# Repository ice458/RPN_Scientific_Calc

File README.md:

# RPN Scientific Calculator
RPN Scientific Calculator with PIC32CM2532LE00048.  
Reverse Polish notation with 4-element stack.  
This calculator uses a proprietary decimal floating point library to perform calculations.  
This project was created using MPLAB X IDE v6.20, XC32 v4.35, and MCC v5.50.  
For more information, please visit [this site.](https://ice458.github.io/project-18775/)

## Demo

## License

This project is licensed under the MIT License. See the [LICENSE](LICENSE) file for details.

## Notice Regarding Third-Party Code

Please note that the copyright of the files contained in the directories [src/packs](src/packs) and [src/config](src/config) does not belong to ice458. These files include code that is subject to third-party licenses. Please refer to the comments at the top of these files for specific licensing information.

The directories [src/packs](src/packs) and [src/config](src/config) may contain files licensed under the Apache License 2.0 and Microchip's proprietary license. You must comply with these licenses when using or distributing these files.

### Apache License 2.0

Portions of this project are licensed under the Apache License 2.0. You may obtain a copy of the License at http://www.apache.org/licenses/LICENSE-2.0.

### Microchip Proprietary License

Certain files are subject to Microchip's proprietary license. These files are provided by Microchip "as is" without any warranties, and you may use Microchip software and any derivatives exclusively with Microchip products. Refer to the comments within the files for more details on the terms and conditions.

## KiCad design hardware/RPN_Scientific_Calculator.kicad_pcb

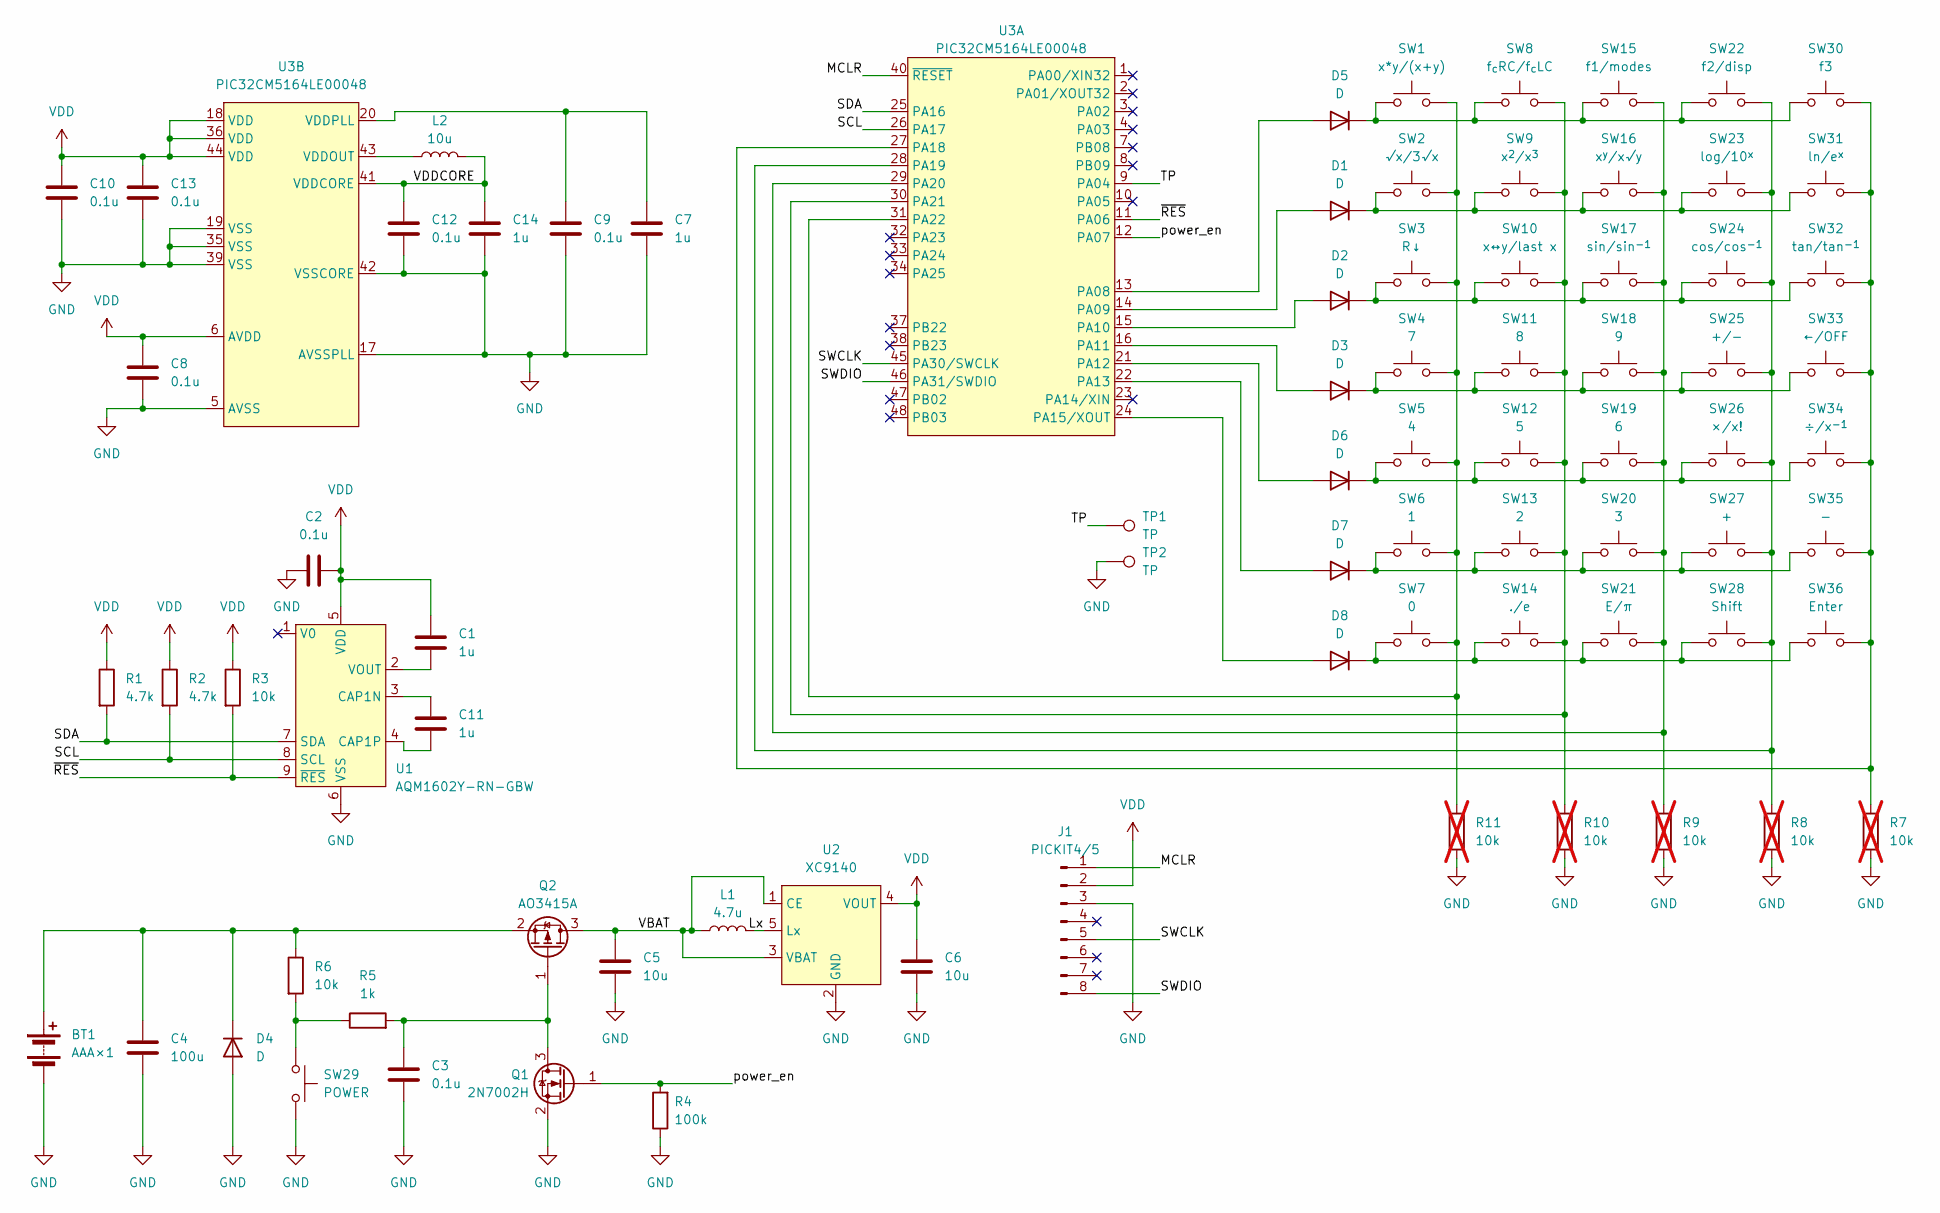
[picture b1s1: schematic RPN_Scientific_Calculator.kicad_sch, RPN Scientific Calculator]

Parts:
BT1: AAA×1; BatteryHolder_Keystone_2466_1xAAA
C1, C7, C11, C14: 1u; C_0603_1608Metric
C2, C3, C8, C9, C10, C12, C13: 0.1u; C_0603_1608Metric
C4: 100u; C_1206_3216Metric
C5, C6: 10u; C_0603_1608Metric
D1, D2, D3, D4, D5, D6, D7, D8: D; D_SOD-123
J1: PICKIT4/5; PinHeader_1x08_P2.54mm_Vertical
L1: 4.7u; L_1008_2520Metric
L2: 10u; L_1008_2520Metric
Q1: 2N7002H; SOT-23
Q2: AO3415A; SOT-23
R1, R2: 4.7k; R_0603_1608Metric
R3, R6: 10k; R_0603_1608Metric
R4: 100k; R_0603_1608Metric
R5: 1k; R_0603_1608Metric
R7, R8, R9, R10, R11: 10k; R_0603_1608Metric; not fitted
SW1: x*y/(x+y); SW_PUSH_6mm
SW2: √x/3√x; SW_PUSH_6mm
SW3: R↓; SW_PUSH_6mm
SW4: 7; SW_PUSH_6mm
SW5: 4; SW_PUSH_6mm
SW6: 1; SW_PUSH_6mm
SW7: 0; SW_PUSH_6mm
SW8: f_{c}RC/f_{c}LC; SW_PUSH_6mm
SW9: x^{2}/x^{3}; SW_PUSH_6mm
SW10: x↔y/last x; SW_PUSH_6mm
SW11: 8; SW_PUSH_6mm
SW12: 5; SW_PUSH_6mm
SW13: 2; SW_PUSH_6mm
SW14: ./e; SW_PUSH_6mm
SW15: f1/modes; SW_PUSH_6mm
SW16: x^{y}/x√y; SW_PUSH_6mm
SW17: sin/sin^{-1}; SW_PUSH_6mm
SW18: 9; SW_PUSH_6mm
SW19: 6; SW_PUSH_6mm
SW20: 3; SW_PUSH_6mm
SW21: E/π; SW_PUSH_6mm
SW22: f2/disp; SW_PUSH_6mm
SW23: log/10^{x}; SW_PUSH_6mm
SW24: cos/cos^{-1}; SW_PUSH_6mm
SW25: +/-; SW_PUSH_6mm
SW26: ×/x!; SW_PUSH_6mm
SW27: +; SW_PUSH_6mm
SW28: Shift; SW_PUSH_6mm
SW29: POWER; SW_PUSH_6mm
SW30: f3; SW_PUSH_6mm
SW31: ln/e^{x}; SW_PUSH_6mm
SW32: tan/tan^{-1}; SW_PUSH_6mm
SW33: ←/OFF; SW_PUSH_6mm
SW34: ÷/x^{-1}; SW_PUSH_6mm
SW35: -; SW_PUSH_6mm
SW36: Enter; SW_PUSH_6mm
TP1, TP2: TP; TestPoint_Pad_D1.0mm
U1: AQM1602Y-RN-GBW
U2: XC9140; SOT-23-5
U3: PIC32CM5164LE00048; TQFP-48_7x7mm_P0.5mm

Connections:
/Lx: L1.2, U2.5 (Lx)
/MCLR: J1.1, U3.40 (~RESET)
/SCL: R2.2, U1.8 (SCL), U3.26 (PA17)
/SDA: R1.2, U1.7 (SDA), U3.25 (PA16)
/SWCLK: J1.5, U3.45 (PA30/SWCLK)
/SWDIO: J1.8, U3.46 (PA31/SWDIO)
/TP: TP1.1, U3.9 (PA04)
/VBAT: C5.2, L1.1, Q2.3 (D), U2.1 (CE), U2.3 (VBAT)
/VDDCORE: C12.2, C14.2, L2.2, U3.41 (VDDCORE)
/power_en: Q1.1 (G), R4.2, U3.12 (PA07)
/~RES: R3.2, U1.9 (~RES), U3.11 (PA06)
GND: BT1.2 (-), C2.1, C3.1, C4.1, C5.1, C6.1, C7.1, C8.1, C9.1, C10.1, C12.1, C13.1, C14.1, D4.2 (A), J1.3, Q1.2 (S), R4.1, R7.2, R8.2, R9.2, R10.2, R11.2, SW29.2, TP2.1, U1.6 (VSS), U2.2 (GND), U3.5 (AVSS), U3.17 (AVSSPLL), U3.19 (VSS), U3.35 (VSS), U3.39 (VSS), U3.42 (VSSCORE)
unnamed: BT1.1 (+), C4.2, D4.1 (K), Q2.2 (S), R6.1
unnamed: D1.2 (A), U3.14 (PA09)
unnamed: D1.1 (K), SW2.1, SW9.1, SW16.1, SW23.1, SW31.1
unnamed: D2.2 (A), U3.15 (PA10)
unnamed: D2.1 (K), SW3.1, SW10.1, SW17.1, SW24.1, SW32.1
unnamed: D3.2 (A), U3.16 (PA11)
unnamed: D3.1 (K), SW4.1, SW11.1, SW18.1, SW25.1, SW33.1
unnamed: D5.2 (A), U3.13 (PA08)
unnamed: D5.1 (K), SW1.1, SW8.1, SW15.1, SW22.1, SW30.1
unnamed: D6.2 (A), U3.21 (PA12)
unnamed: D6.1 (K), SW5.1, SW12.1, SW19.1, SW26.1, SW34.1
unnamed: D7.2 (A), U3.22 (PA13)
unnamed: D7.1 (K), SW6.1, SW13.1, SW20.1, SW27.1, SW35.1
unnamed: D8.2 (A), U3.24 (PA15/XOUT)
unnamed: D8.1 (K), SW7.1, SW14.1, SW21.1, SW28.1, SW36.1
unnamed: C3.2, Q1.3 (D), Q2.1 (G), R5.2
unnamed: R5.1, R6.2, SW29.1
unnamed: C11.2, U1.3 (CAP1N)
unnamed: C11.1, U1.4 (CAP1P)
unnamed: C1.1, U1.2 (VOUT)
unnamed: R7.1, SW30.2, SW31.2, SW32.2, SW33.2, SW34.2, SW35.2, SW36.2, U3.27 (PA18)
unnamed: R8.1, SW22.2, SW23.2, SW24.2, SW25.2, SW26.2, SW27.2, SW28.2, U3.28 (PA19)
unnamed: R9.1, SW15.2, SW16.2, SW17.2, SW18.2, SW19.2, SW20.2, SW21.2, U3.29 (PA20)
unnamed: R10.1, SW8.2, SW9.2, SW10.2, SW11.2, SW12.2, SW13.2, SW14.2, U3.30 (PA21)
unnamed: R11.1, SW1.2, SW2.2, SW3.2, SW4.2, SW5.2, SW6.2, SW7.2, U3.31 (PA22)
unnamed: L2.1, U3.43 (VDDOUT)
unnamed: C7.2, C9.2, U3.20 (VDDPLL)
VDD: C1.2, C2.2, C6.2, C8.2, C10.2, C13.2, J1.2, R1.1, R2.1, R3.1, U1.5 (VDD), U2.4 (VOUT), U3.6 (AVDD), U3.18 (VDD), U3.36 (VDD), U3.44 (VDD)

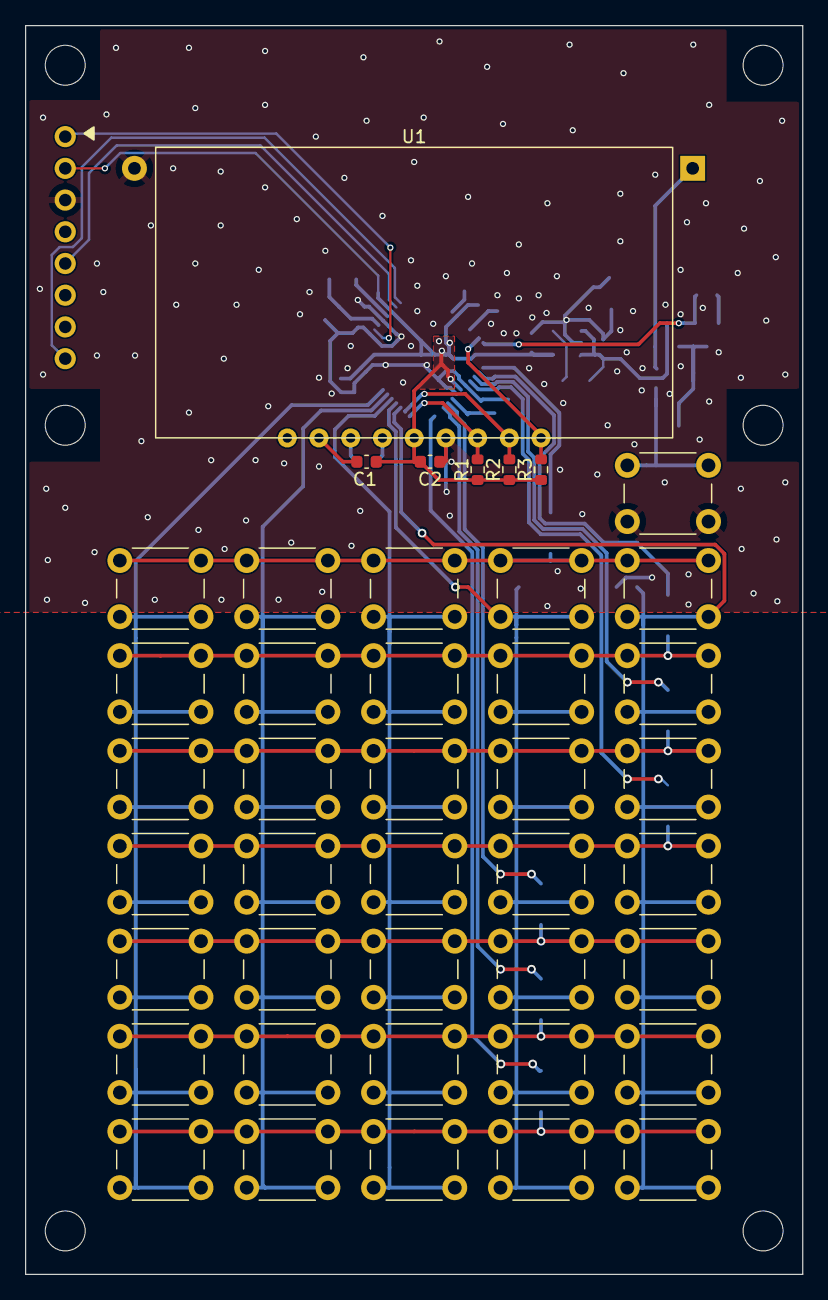
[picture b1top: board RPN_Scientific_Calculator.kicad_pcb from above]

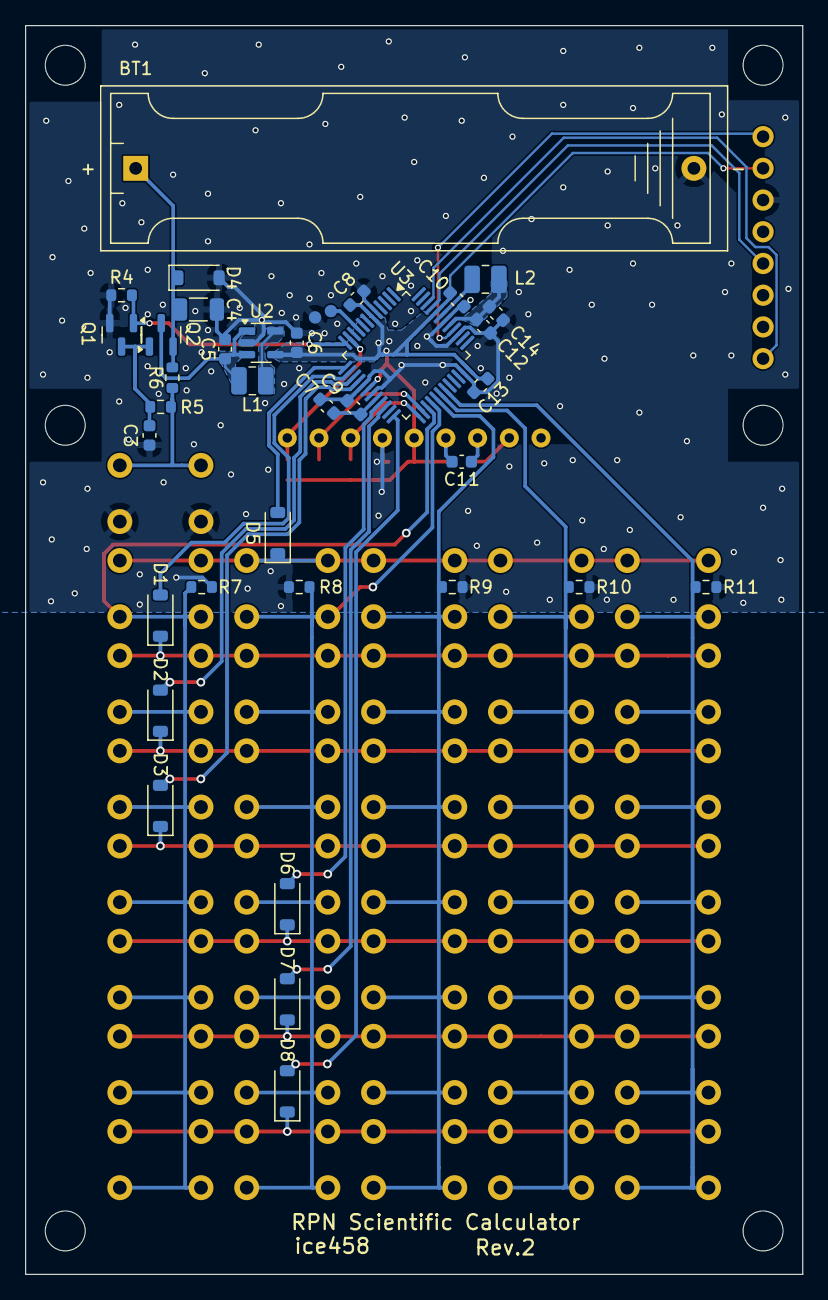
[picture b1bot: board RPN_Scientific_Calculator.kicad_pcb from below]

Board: 2 copper layers, 62.2 x 100.0 mm, 86 parts (37 on the bottom side), 40 nets.

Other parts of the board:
REF1, REF2, REF3, REF4, REF5, REF6: MountingHole_3.2mm_M3

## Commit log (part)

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2024-06-29 回路図の修正
2024-06-29 Add BOM
2024-07-02 三角関数の精度向上
2024-07-02 足し算の結果が負のゼロになる問題を修正
2024-07-02 三角関数が±1の範囲に収まるように修正
2024-07-02 設定画面から戻ったときに数値の入力を続行できるよう変更
2024-07-02 df_roundのバグ修正
2024-07-02 LASTキーの挙動を修正
2024-07-02 n th root のエラー処理を追加
2024-07-02 対数のエラー処理を実装
2024-07-03 内部計算桁数を12から18に変更
2024-07-04 expを改善
2024-07-04 対数の改善
2024-07-04 config
2024-08-20 sqrt(0)と、負数のcbrtが正しく計算されない問題を修正
2025-02-02 0-0やlnのバグ修正、WDTの追加
2025-02-02 設定変更ができないバグを修正
2025-04-20 計算精度の改善 (ただしデバッグは不十分なので注意)
2025-04-23 逆数を計算済みにしておく
2025-04-23 MCC Coreバージョンアップ
2025-07-02 gitignore
2025-07-02 リファクタリングとバグ修正
2025-07-02 物理定数の機能を追加
2025-07-02 リファクタリング
2025-07-04 安全性の向上
